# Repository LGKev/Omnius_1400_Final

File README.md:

# Omnius_1400_Final
Code Repository I develop for the ECE1400 Final.

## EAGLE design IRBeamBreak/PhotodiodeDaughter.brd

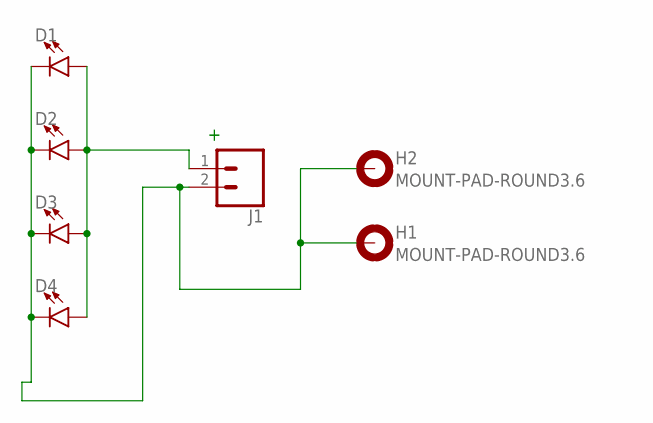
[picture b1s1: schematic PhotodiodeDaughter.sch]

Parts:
D1, D2, D3, D4: LED3MM; LED_3MM
H1, H2: MOUNT-PAD-ROUND3.6; 3,6-PAD
J1: CONN_02; 1X02

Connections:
+: D1.A, D2.A, D3.A, D4.A, J1.1
-: D1.K (C), D2.K (C), D3.K (C), D4.K (C), H1.B3,6, H2.B3,6, J1.2

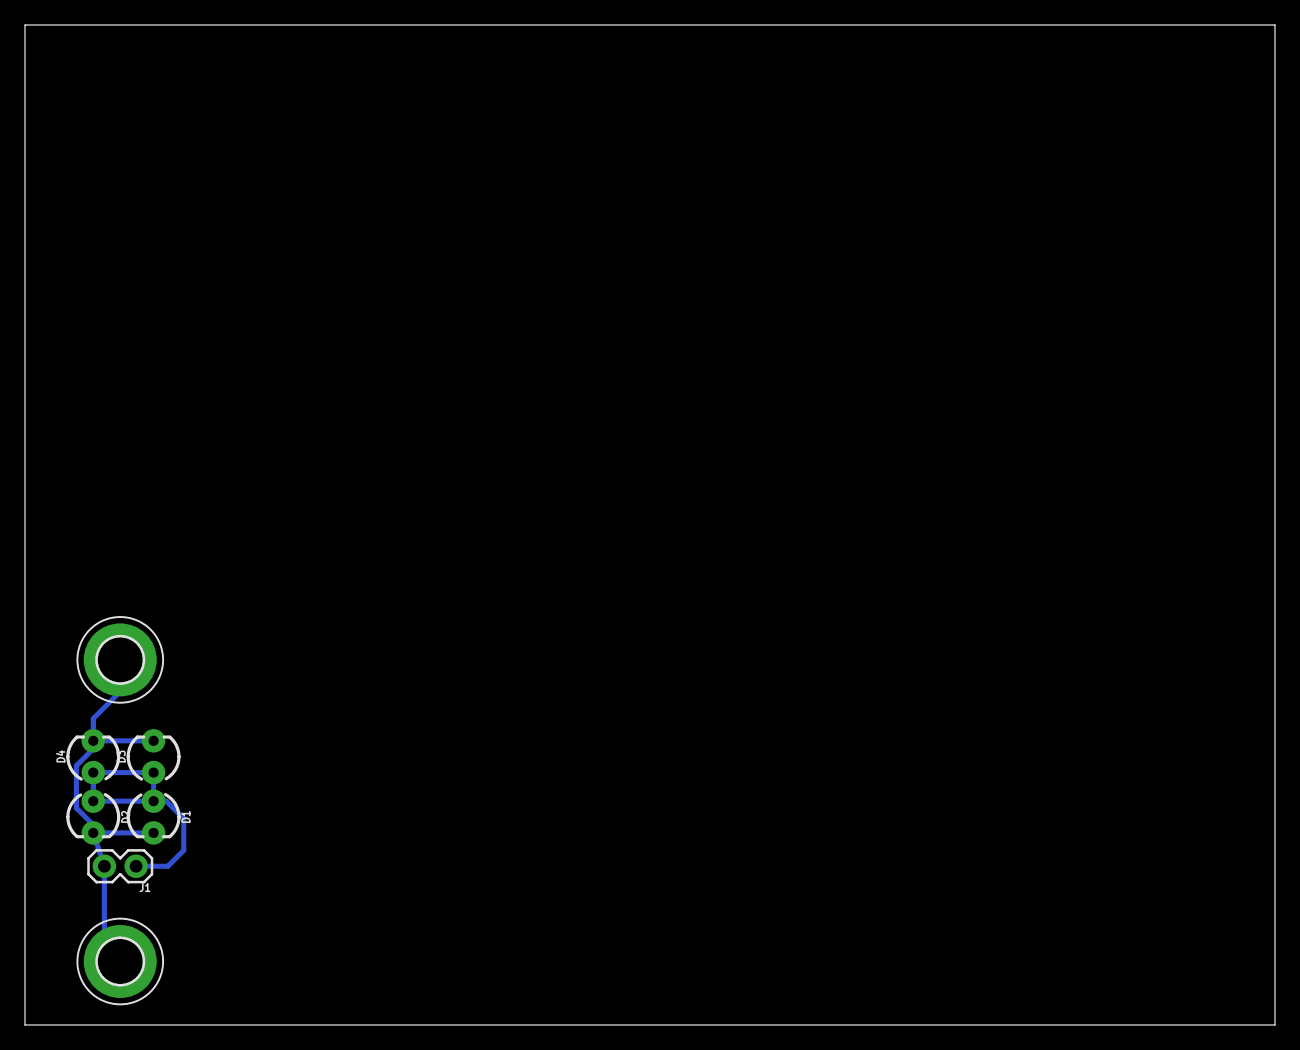
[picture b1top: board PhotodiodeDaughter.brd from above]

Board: 2 copper layers, 100.0 x 80.0 mm, 7 parts (0 on the bottom side), 2 nets.

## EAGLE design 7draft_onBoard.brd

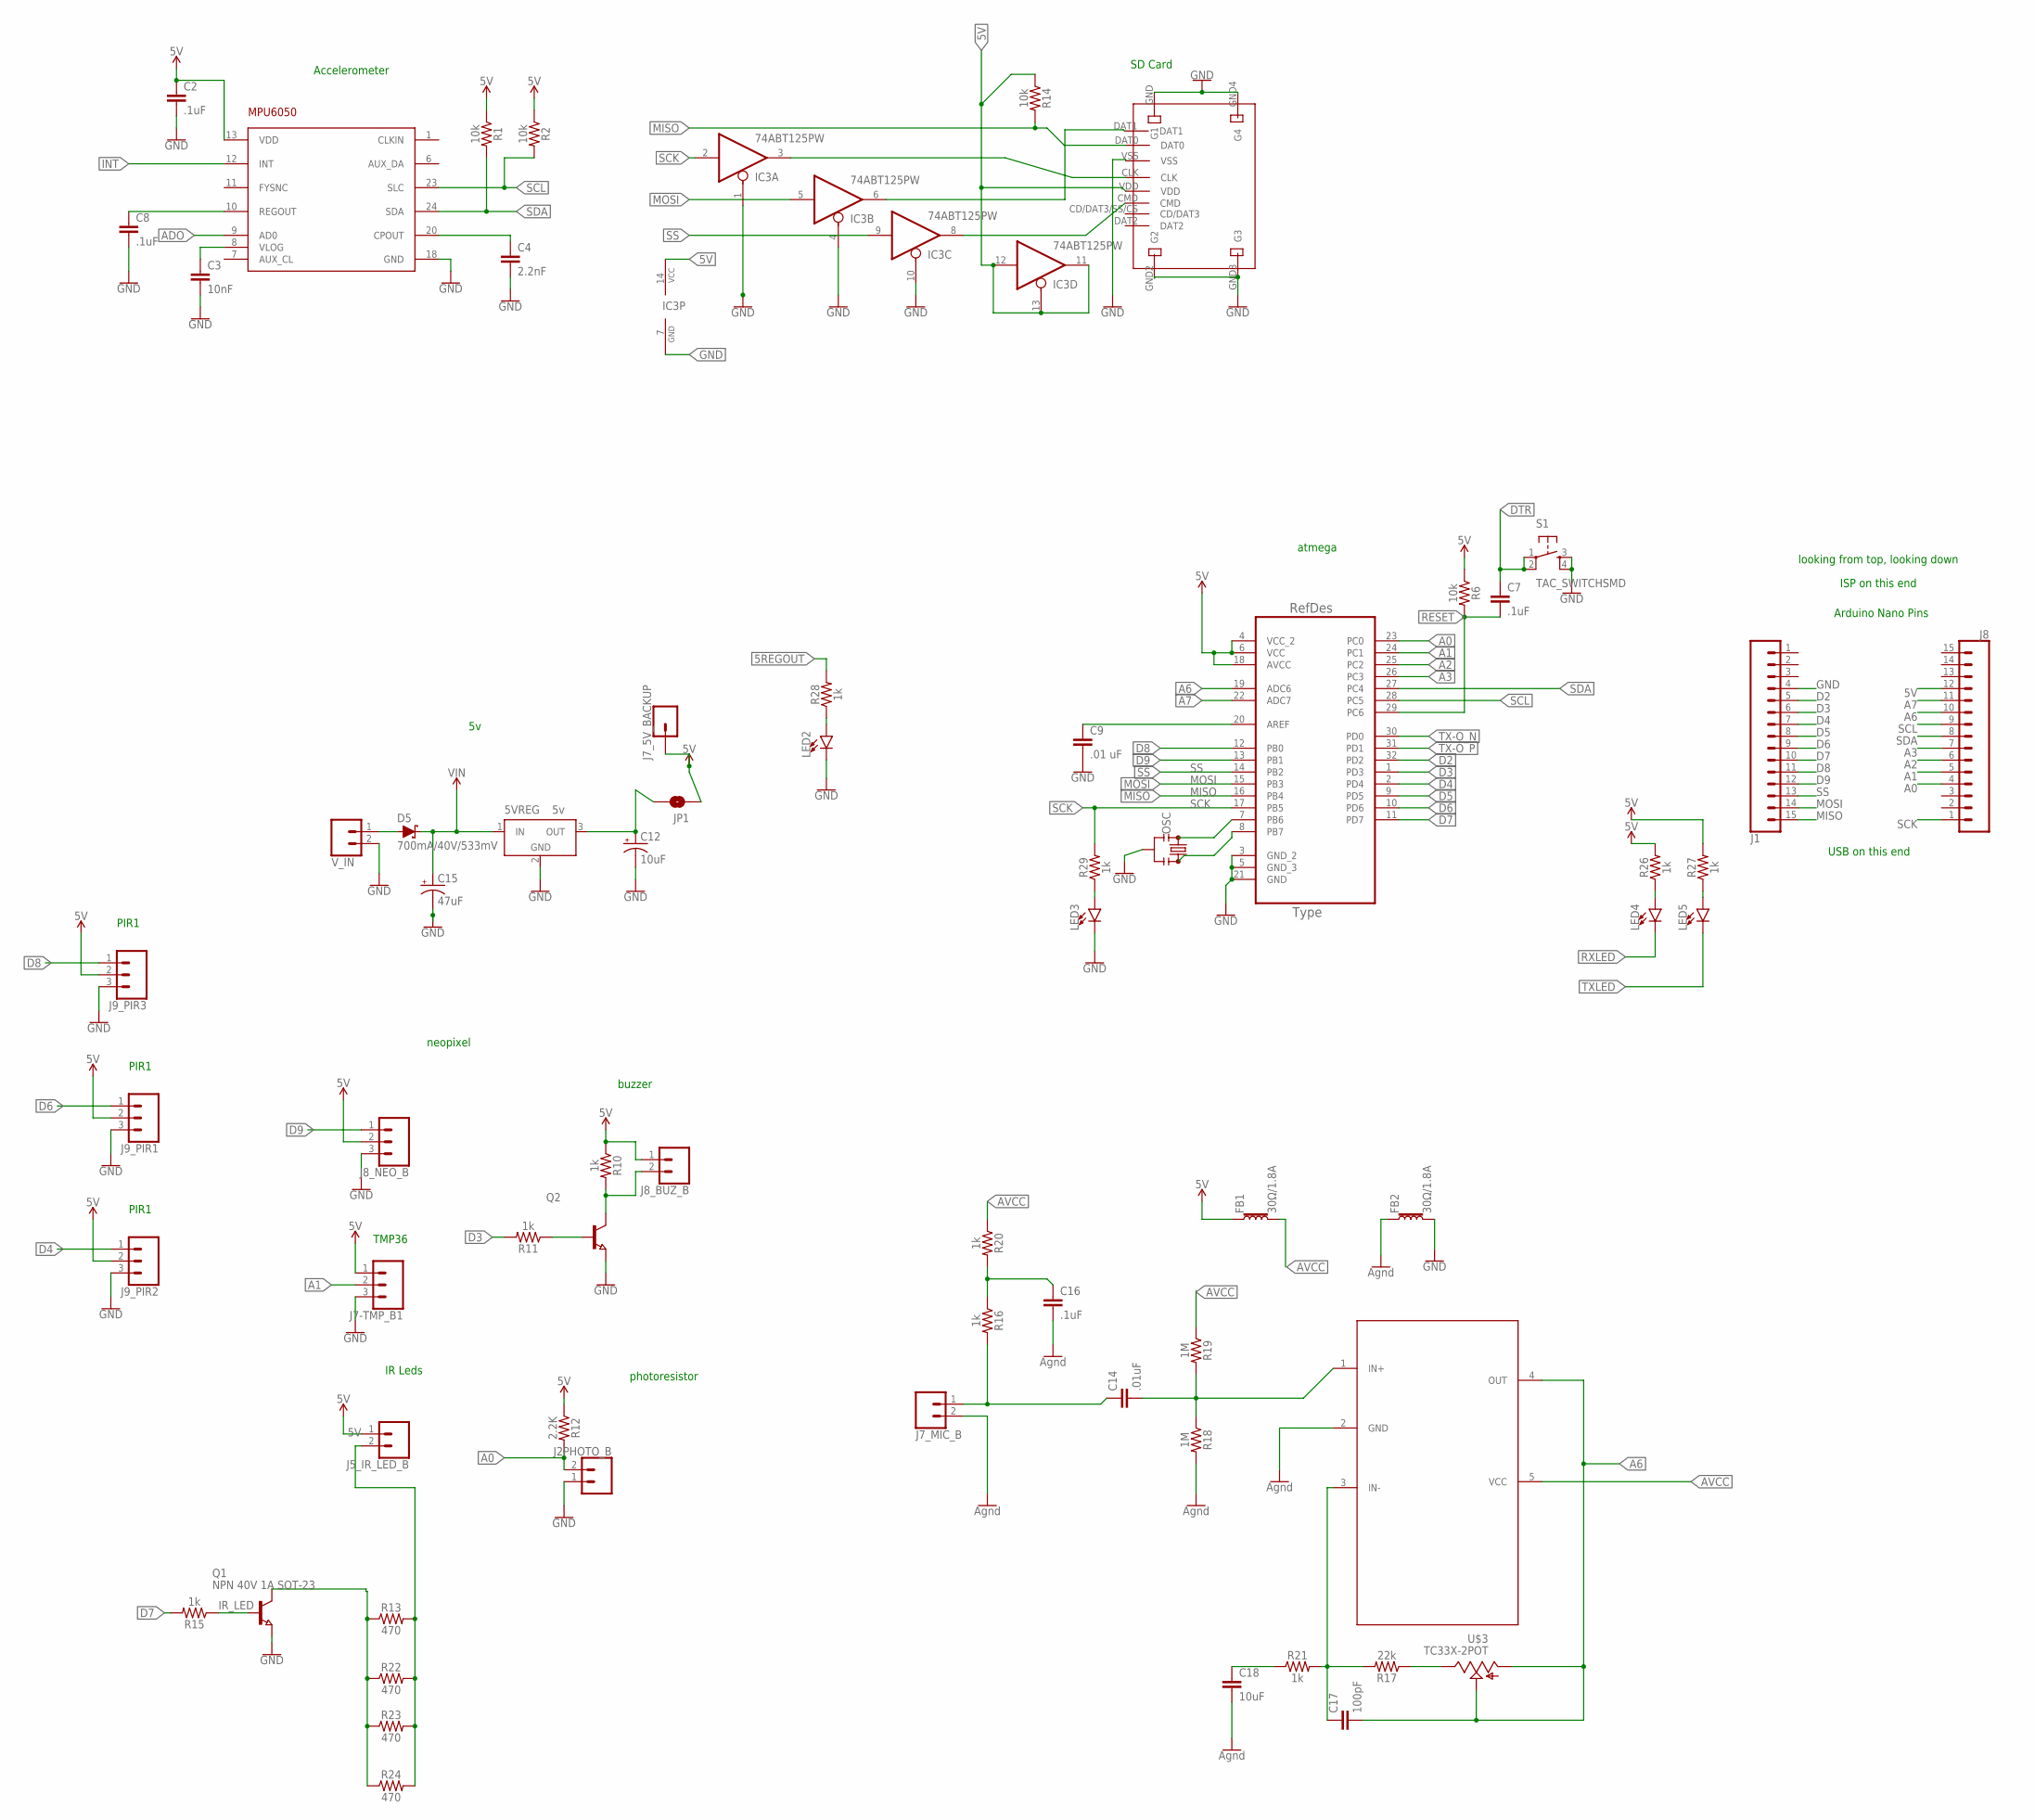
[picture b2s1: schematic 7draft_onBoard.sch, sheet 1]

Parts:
5VREG: 5v; SOT223
ATMEGA328P-AU: ATMEGA328P-AU; QFP80P900X900X120-32N
C2, C7, C8, C16: .1uF; 0402-CAP
C3: 10nF; 0402-CAP
C4: 2.2nF; 0402-CAP
C9: .01 uF; 0402-CAP
C12: 10uF; EIA3216
C14: .01uF; 0402-CAP
C15: 47uF; EIA3216
C17: 100pF; 0402-CAP
C18: 10uF; 0402-CAP
D5: 700mA/40V/533mV; SOT23-3
FB1, FB2: 30Ω/1.8A; 0603
IC3: 74ABT125PW; TSSOP14
IC4: MAX4466KS; SC70-5
J1, J8: CONN_15; 1X15
J2PHOTO_B, J5_IR_LED_B, J7_MIC_B, J8_BUZ_B: CONN_02LOCK; 1X02_LOCK
J7-TMP_B1, J8_NEO_B, J9_PIR1, J9_PIR2, J9_PIR3: CONN_03; 1X03
J7_5V_BACKUP: CONN_01; 1X01
JP1: JUMPER-SMT_2_NO_NO-SILK_ROUND; SMT-JUMPER_2_NO_NO-SILK_ROUND
LED2, LED3, LED4, LED5: LED0603; LED-0603
MPU6050: MPU-6050; QFN24-4X4
OSC: RESONATORSMD-3.2X1.3; RESONATOR-SMD-3.2X1.3
Q1: NPN 40V 1A SOT-23; SOT23
Q2: NPN-TRANSISTOR_SOT23; SOT23
R1, R2, R6, R14: 10k; 0603
R10, R11, R15, R16, R20, R21, R26, R27, R28, R29: 1k; 0603
R12: 2.2K; 0603
R13, R22, R23, R24: 470; 0603
R17: 22k; 0603
R18, R19: 1M; 0603
S1: TAC_SWITCHSMD; TACTILE-SWITCH-SMD
U$2: WM6698TR-ND_MICROSD; MICROSD2
U$3: TC33X-2POT; TC33X-2
V_IN: CONN_02LOCK; 1X02_LOCK

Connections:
2.2NF: C4.1, MPU6050.20 (CPOUT)
5REGOUT: 5VREG.3 (OUT), C12.A (+), JP1.2, R28.2
5V: ATMEGA328P-AU.4 (VCC_2), ATMEGA328P-AU.6 (VCC), ATMEGA328P-AU.18 (AVCC), C2.1, FB1.1, IC3.11 (O), IC3.12 (I), IC3.13 (OE), IC3.14 (VCC), J5_IR_LED_B.1, J7-TMP_B1.1, J7_5V_BACKUP.1, J8.12, J8_BUZ_B.1, J8_NEO_B.2, J9_PIR1.2, J9_PIR2.2, J9_PIR3.2, JP1.1, MPU6050.13 (VDD), R1.1, R2.1, R6.1, R10.1, R12.1, R14.1, R26.2, R27.2, U$2.VDD; also elsewhere on the board
10NF: C3.1, MPU6050.8 (VLOG)
.UF: C8.1, MPU6050.10 (REGOUT)
A0: ATMEGA328P-AU.23 (PC0), J2PHOTO_B.2, J8.4, R12.2
A1: ATMEGA328P-AU.24 (PC1), J7-TMP_B1.2, J8.5
A2: ATMEGA328P-AU.25 (PC2), J8.6
A3: ATMEGA328P-AU.26 (PC3), J8.7
A6: ATMEGA328P-AU.19 (ADC6), C17.2, IC4.4 (OUT), J8.10, U$3.2, U$3.3
A7: ATMEGA328P-AU.22 (ADC7), J8.11
ADO: MPU6050.9 (AD0)
AVCC: FB1.2, IC4.5 (VCC), R19.1, R20.1
BUZ-: J8_BUZ_B.2, Q2.3 (C), R10.2
D2: ATMEGA328P-AU.32 (PD2), J1.5
D3: ATMEGA328P-AU.1 (PD3), J1.6, R11.2
D4: ATMEGA328P-AU.2 (PD4), J1.7, J9_PIR2.1
D5: ATMEGA328P-AU.9 (PD5), J1.8
D6: ATMEGA328P-AU.10 (PD6), J1.9, J9_PIR1.1
D7: ATMEGA328P-AU.11 (PD7), J1.10, R15.2
D8: ATMEGA328P-AU.12 (PB0), J1.11, J9_PIR3.1
D9: ATMEGA328P-AU.13 (PB1), J1.12, J8_NEO_B.1
DAT1: IC3.6 (O), U$2.DAT1
DTR: C7.1, S1.1, S1.2; also elsewhere on the board
GND: 5VREG.2 (GND), 5VREG.4 (GND), ATMEGA328P-AU.3 (GND_2), ATMEGA328P-AU.5 (GND_3), ATMEGA328P-AU.21 (GND), C2.2, C3.2, C4.2, C8.2, C9.2, C12.C (-), C15.C (-), C16.2, C18.2, FB2.1, FB2.2, IC3.1 (OE), IC3.4 (OE), IC3.7 (GND), IC3.10 (OE), IC4.2 (GND), J1.4, J2PHOTO_B.1, J7-TMP_B1.3, J7_MIC_B.2, J8_NEO_B.3, J9_PIR1.3, J9_PIR2.3, J9_PIR3.3, LED2.C, LED3.C, MPU6050.18 (GND), OSC.2, Q1.2 (E), Q2.2 (E), R18.2, S1.3, S1.4, U$2.GND (G1), U$2.GND2 (G2), U$2.GND3 (G3), U$2.GND4 (G4), U$2.VSS, V_IN.2; also elsewhere on the board
INT: MPU6050.12 (INT)
IR_LED: Q1.1 (B), R15.1
LED4: LED4.A, R26.1
LED5: LED5.A, R27.1
MICNET1K: C16.1, R16.1, R20.2
MIC_IN+: C14.2, IC4.1 (IN+), R18.1, R19.2
MIC_IN_C14: C14.1, J7_MIC_B.1, R16.2
MISO: ATMEGA328P-AU.16 (PB4), J1.15, R14.2, U$2.DAT0
MOSI: ATMEGA328P-AU.15 (PB3), IC3.5 (I), J1.14
unnamed: J5_IR_LED_B.2, R13.2, R22.2, R23.2, R24.2
unnamed: Q1.3 (C), R13.1, R22.1, R23.1, R24.1
unnamed: LED3.A, R29.1
unnamed: ATMEGA328P-AU.20 (AREF), C9.1
unnamed: R17.1, U$3.1
unnamed: Q2.1 (B), R11.1
unnamed: D5.1 (A), V_IN.1
unnamed: C18.1, R21.1
unnamed: C17.1, IC4.3 (IN-), R17.2, R21.2
PB6: ATMEGA328P-AU.7 (PB6), OSC.1
PB7: ATMEGA328P-AU.8 (PB7), OSC.3
POWERLED: LED2.A, R28.1
RESET: ATMEGA328P-AU.29 (PC6), C7.2, R6.2
RXLED: LED4.C; also elsewhere on the board
SCK: ATMEGA328P-AU.17 (PB5), IC3.2 (I), J8.1, R29.2
SCK_BUFF: IC3.3 (O), U$2.CLK
SCL: ATMEGA328P-AU.28 (PC5), J8.9, MPU6050.23 (SLC), R2.2
SDA: ATMEGA328P-AU.27 (PC4), J8.8, MPU6050.24 (SDA), R1.2
SS: ATMEGA328P-AU.14 (PB2), IC3.9 (I), J1.13
SS_BUFF: IC3.8 (O), U$2.CMD
TX-O_N: ATMEGA328P-AU.30 (PD0); also elsewhere on the board
TX-O_P: ATMEGA328P-AU.31 (PD1); also elsewhere on the board
TXLED: LED5.C; also elsewhere on the board
VIN: 5VREG.1 (IN), C15.A (+), D5.3 (C)

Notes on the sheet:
Accelerometer
SD Card
atmega
neopixel
TMP36
IR Leds
buzzer
photoresistor
Arduino Nano Pins
USB on this end
ISP on this end
looking from top, looking down
PIR1

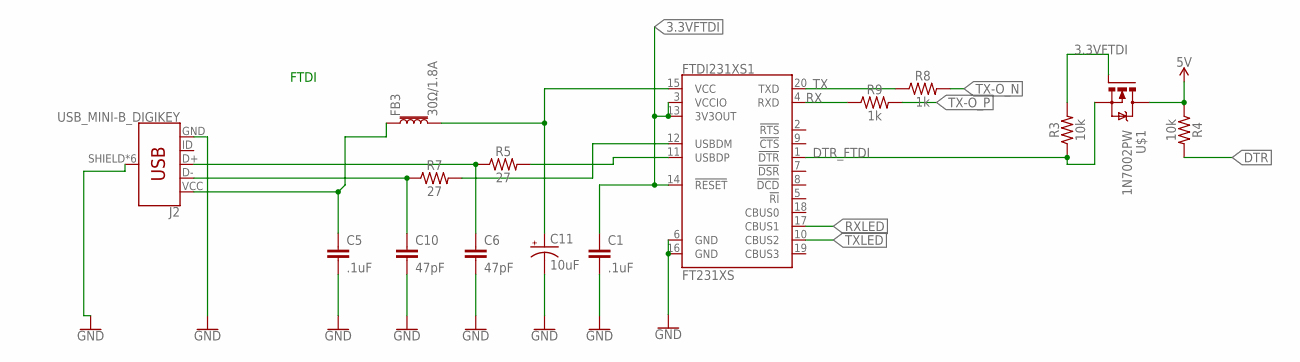
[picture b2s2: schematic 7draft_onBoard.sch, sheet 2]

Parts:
C1, C5: .1uF; 0402-CAP
C6, C10: 47pF; 0402-CAP
C11: 10uF; EIA3216
FB3: 30Ω/1.8A; 0603
FTDI231XS1: FT231XS; SSOP20_L
J2: USB_MINI-B_DIGIKEY; MICRO-USB-DIGIKEY-FCI2
R3, R4: 10k; 0603
R5, R7: 27; 0603
R8, R9: 1k; 0603
U$1: 1N7002PW; SOT323W_INFINEON

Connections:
3.3VFTDI: C1.1, FTDI231XS1.3 (VCCIO), FTDI231XS1.13 (3V3OUT), FTDI231XS1.14 (!RESET), R3.2, U$1.1 (G)
5V: R4.1, U$1.3 (D); also elsewhere on the board
DN_N: C10.1, J2.D-, R7.1
DN_P: C6.1, J2.D+, R5.1
DTR: R4.2; also elsewhere on the board
DTR_FTDI: FTDI231XS1.1 (!DTR), R3.1, U$1.2 (S)
GND: C1.2, C5.2, C6.2, C10.2, C11.C (-), FTDI231XS1.6 (GND), FTDI231XS1.16 (GND), J2.GND, J2.SHIELD, J2.SHIELD1 (SHIELD), J2.SHIELD2 (SHIELD), J2.SHIELD3 (SHIELD), J2.SHIELD4 (SHIELD), J2.SHIELD5 (SHIELD); also elsewhere on the board
RX: FTDI231XS1.4 (RXD), R9.1
RXLED: FTDI231XS1.17 (CBUS1); also elsewhere on the board
TX: FTDI231XS1.20 (TXD), R8.1
TX-O_N: R8.2; also elsewhere on the board
TX-O_P: R9.2; also elsewhere on the board
TXLED: FTDI231XS1.10 (CBUS2); also elsewhere on the board
USBD_N: FTDI231XS1.12 (USBDM), R7.2
USBD_P: FTDI231XS1.11 (USBDP), R5.2
VUSB: C5.1, C11.A (+), FB3.1, FB3.2, FTDI231XS1.15 (VCC), J2.VCC (VBUS)

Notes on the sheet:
FTDI

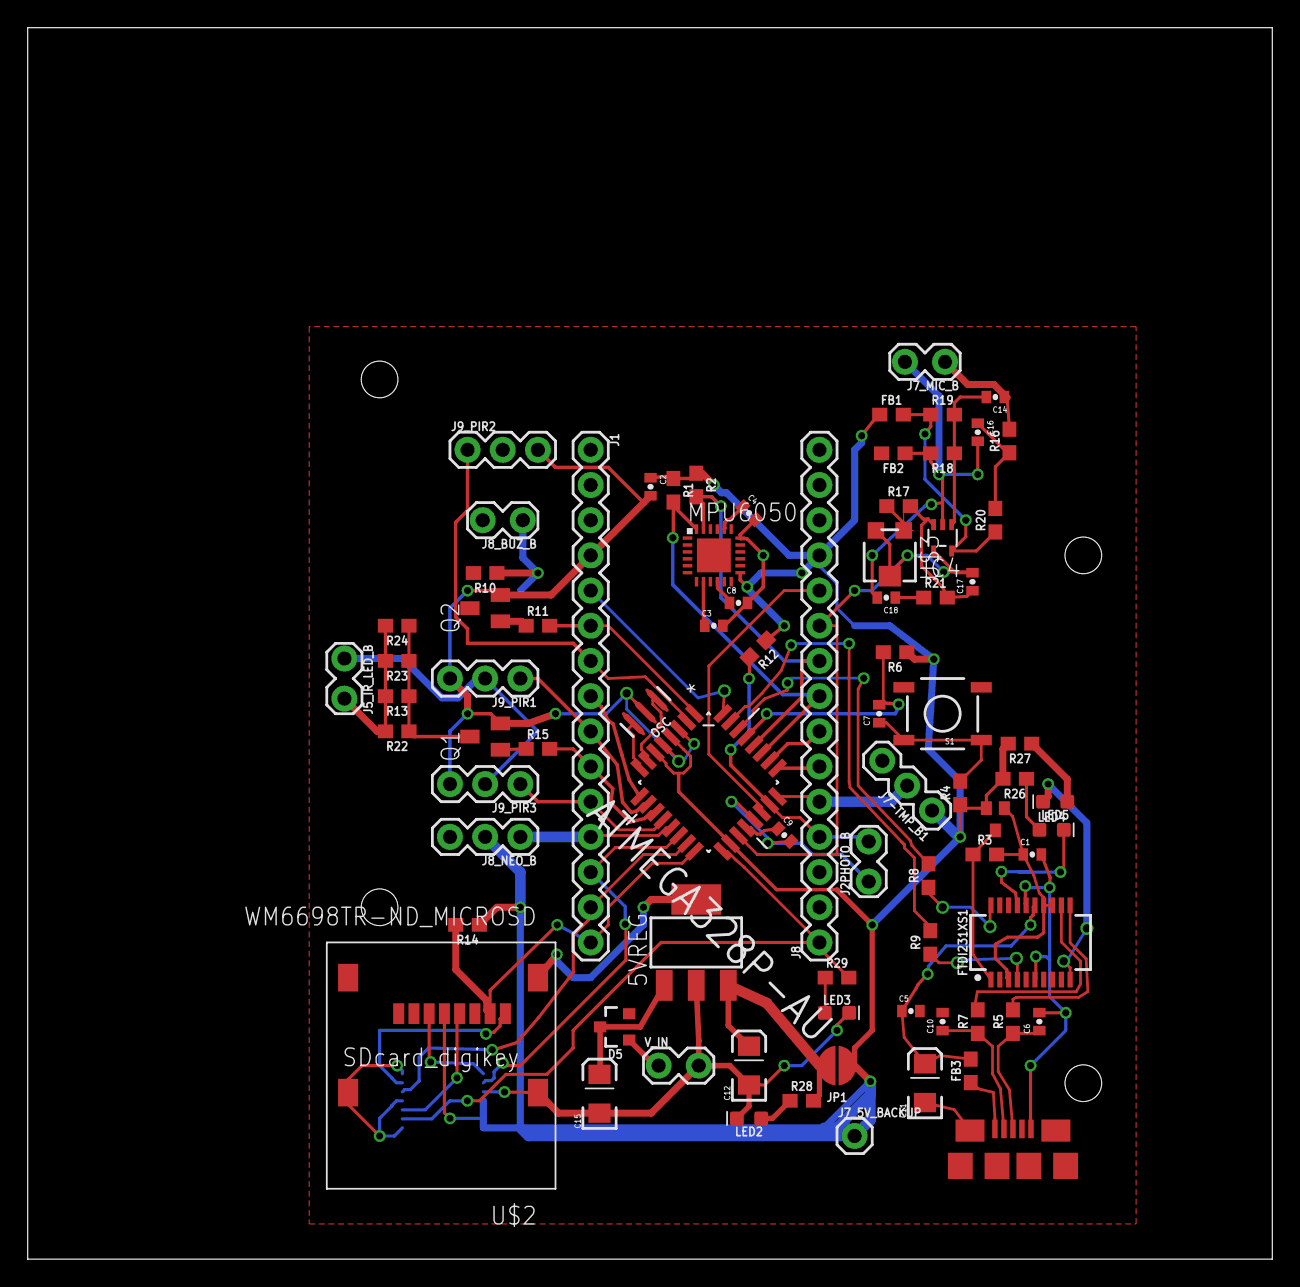
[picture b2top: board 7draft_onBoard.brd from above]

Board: 2 copper layers, 89.8 x 88.9 mm, 81 parts (1 on the bottom side), 65 nets.

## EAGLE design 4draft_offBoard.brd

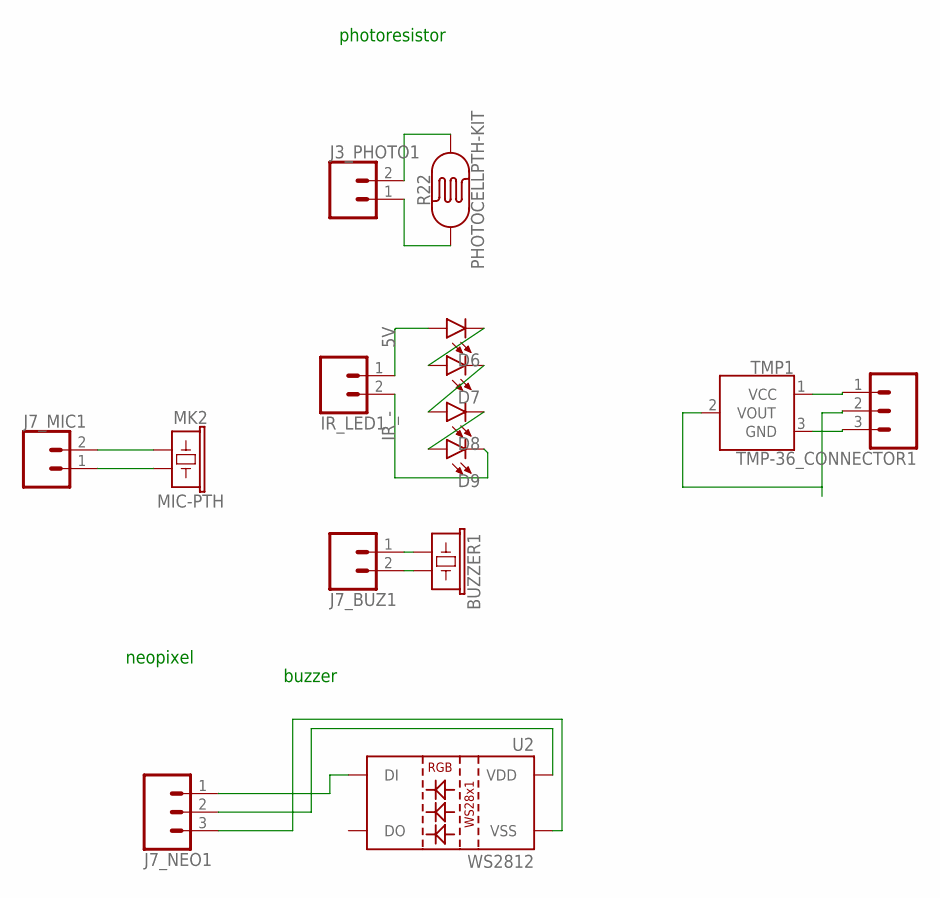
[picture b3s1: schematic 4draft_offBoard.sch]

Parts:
BUZZER1: BUZZER-PTH; BUZZER-12MM
D6, D7, D8, D9: LED-IRTSAL6100; LED_5MM
IR_LED1: CONN_02LOCK; 1X02_LOCK
J3_PHOTO1, J7_BUZ1, J7_MIC1: CONN_02LOCK; 1X02_LOCK
J7_NEO1: CONN_03; 1X03
MK2: MIC-PTH; MICROPHONE-PTH-9.7MM
R22: PHOTOCELLPTH-KIT; PHOTOCELL-KIT
TMP1: TMP36GT9; TO-92
TMP-36_CONNECTOR1: CONN_03; 1X03
U2: WS2812; LED-TRICOLOR-5050-IC

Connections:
5V: D6.A, IR_LED1.1
5V1: J7_NEO1.1, U2.2 (DI)
A4: J3_PHOTO1.2, R22.2
BUZ+1: BUZZER1.+ (1), J7_BUZ1.1
BUZ-1: BUZZER1.- (2), J7_BUZ1.2
D1: J7_NEO1.2, U2.3 (VDD), U2.5 (VDD)
GND1: J3_PHOTO1.1, R22.1
GND2: J7_NEO1.3, U2.6 (VSS)
IR_-: D9.K (C), IR_LED1.2
unnamed: D6.K (C), D7.A
unnamed: D7.K (C), D8.A
unnamed: D8.K (C), D9.A
unnamed: J7_MIC1.1, MK2.GND (2)
unnamed: J7_MIC1.2, MK2.OUT (1)
unnamed: TMP1.1 (VCC), TMP-36_CONNECTOR1.1
unnamed: TMP1.3 (GND), TMP-36_CONNECTOR1.3
unnamed: TMP1.2 (VOUT), TMP-36_CONNECTOR1.2

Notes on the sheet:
photoresistor
buzzer
neopixel

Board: 2 copper layers, 15 parts (0 on the bottom side), 17 nets, no tracks yet.

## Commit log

2017-03-27 Omnius GY-521 implementation
    Based on code from Arduino User JohnChi I was able to create a test file to determine if changes in position were made based on accelerometer data.
    Future versions will use data from, all 3 axis from Accelerometer and the Gyro.
    In addition it will use a better event triggering system.
    Libraries used:
    Wire.h
2017-03-27 I added wiring details
2017-03-28 Second commit
2017-03-28 update pir code
2017-03-29 update pir sensor code to use digital read instead of analog read to save a pin
2017-03-30 Adding schematic and board layout
2017-03-30 update of board
2017-03-30 updated board with more components
2017-03-30 sd card added
2017-03-30 sd card fully laid out
2017-03-31 adding nano header pins
2017-03-31 added mic circuit to A6
2017-03-31 added connector for mic
2017-03-31 separated schematic in terms of items on board and off board so I could start to route
2017-03-31 started board layout
2017-03-31 shrinking board llayout
2017-03-31 re arranging nano layout
2017-03-31 removed 3.3v and changed buffer to be 5v
2017-04-01 adding pir sensors to board
2017-04-01 redoing layout, condensing.
2017-04-01 need to add sensors next
2017-04-01 3rd draft, close to final. FTDI might need to be reworked. and there is a bug. I do not know why AVCC is routed to VCC when it should not be, cannot find net causing issue
2017-04-01 Rx, TX, and FTDI 3.3v traces are very difficult to route at this time. Also need to do ground planes
2017-04-01 Ground planes should be the last thing, and doulbe check the RX Tx of FTDI to processor
2017-04-01 routed, with pour. need to eddit quad buffer to be correct. Lots of DRC and ERC errors. Will start over
2017-04-01 changed the IR led's to be in parallel with 470 ohm resistors
2017-04-01 added led's so we know when board has power and is able to blink
2017-04-01 added leds for RX, TX, power
2017-04-01 less condensed version, indicator leds. and more resistors for IR led
2017-04-01 Almost done, wanted to save before I change the IR leds to an equivalent resistance or a resistor array.
2017-04-02 everything is added. IR fixed, beam break fixed. neo pixel added for fun this will be addressed at 1 and the one at top is addressed at 2
2017-04-24 code base for the 1400 final

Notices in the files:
parts and their libraries:
SparkFun-Electromechanical: Licensing: Creative Commons ShareAlike 4.0 International - https://creativecommons.org/licenses/by-sa/4.0
